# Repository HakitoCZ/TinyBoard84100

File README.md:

# TinyBoard84100

Tiny beakout board for the ATtiny841 (or any other 14 pin
AVR) with AVR ISP programming header, voltage regulated and
with reset button.

It is programmable with the Arduino IDE with the ATtiny
library addon thingy. Or a proper toolchain for all the
tryhard nerds out there :)

Designed in KiCAD open-source and possibly for sale on Tindie
somewhere in the future. No promisses.

It's actually a second version of the design, first was not
published nor tested. It was designed, manufactured and forgoten about.

If you're experienced and want to tell me how wrong I did
everything, feel free to PM me. I'm open to your feedback.

Q: What's so special about the ATtiny841?

A: Compared to ATtiny84, the ATtiny841 has one extra 16-bit
timer with two PWM channels, one more
ADC, more input channels, one extra comparator, one extra USART.
And for more details go check Microchip's product site.
If you want to build it yourself, ATtiny84 seem to be pin compatible
so you should be just fine using that if you want to shave off
few cents and/or don't need the extra functionality of 841.

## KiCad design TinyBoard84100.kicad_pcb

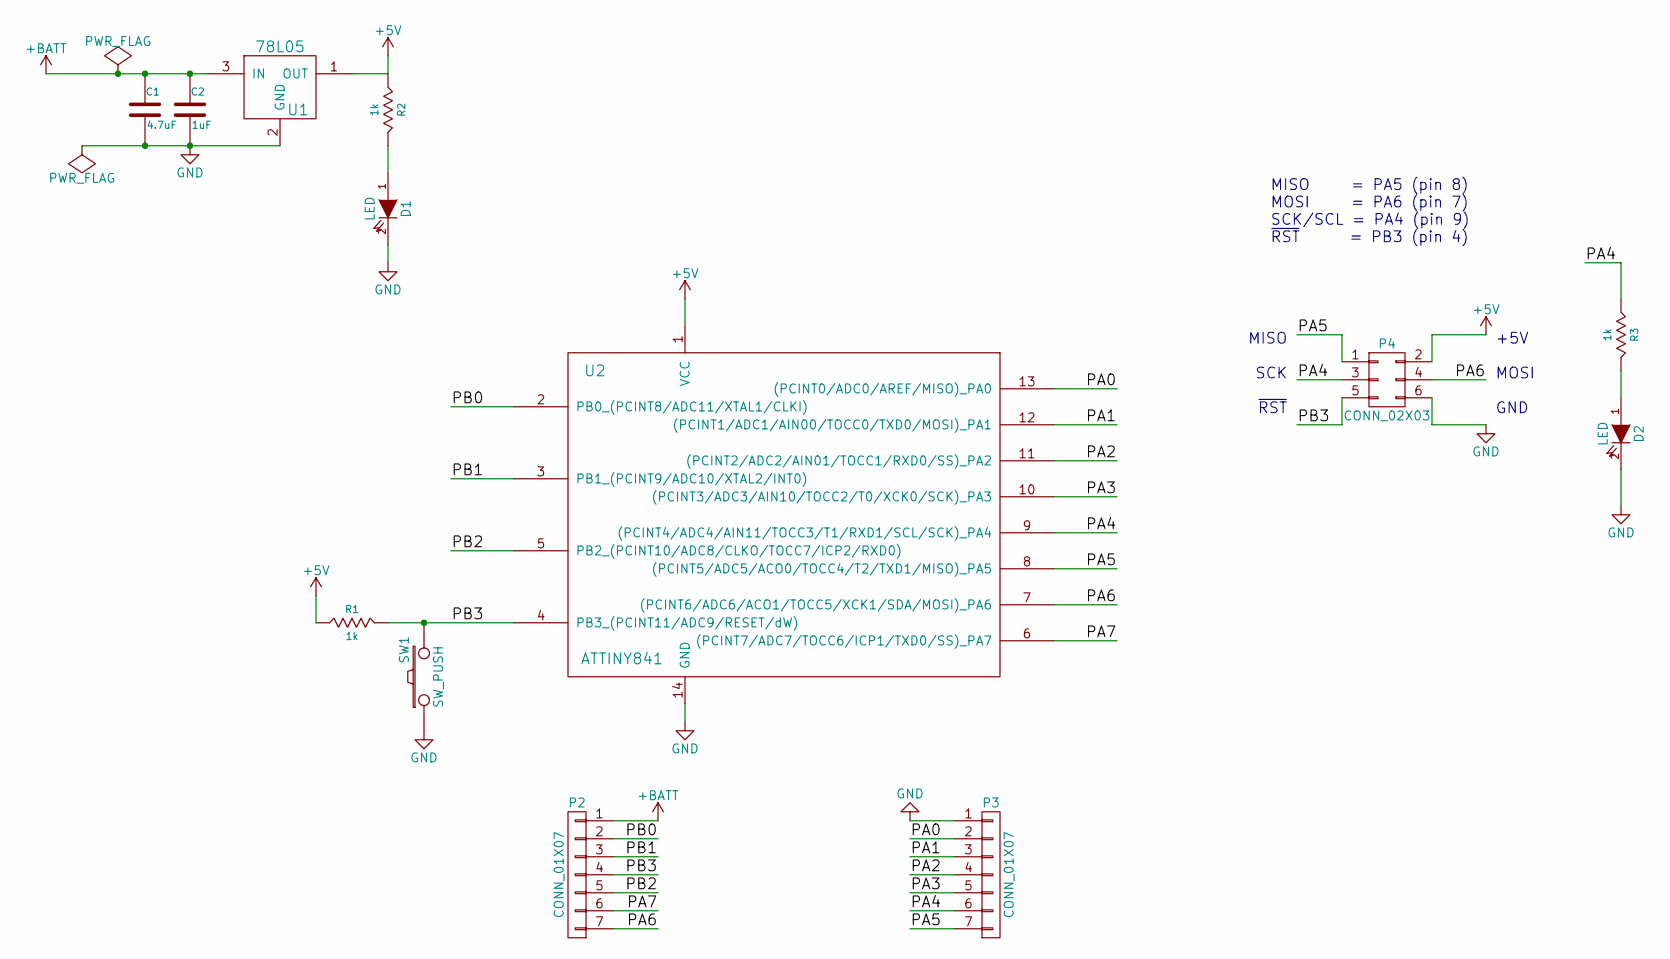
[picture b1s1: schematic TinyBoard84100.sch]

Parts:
C1: 4.7uF; C_1206_HandSoldering
C2: 1uF; C_1206_HandSoldering
D1, D2: LED; LED_0805
P2, P3: CONN_01X07; Pin_Header_Straight_1x07
P4: CONN_02X03; Pin_Header_Straight_2x03
R1, R2, R3: 1k; R_0805_HandSoldering
SW1: SW_PUSH; SW_SPST_FSMSM
U1: 78L05; SOT89-3_Housing_Handsoldering
U2: ATTINY841; SOIC-14_3.9x8.7mm_Pitch1.27mm

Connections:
+5V: P4.2, R1.1 (A), R2.1 (A), U1.1 (OUT), U2.1 (VCC)
+BATT: C1.1, C2.1, P2.1, U1.3 (IN)
/PA0: P3.2, U2.13 ((PCINT0/ADC0/AREF/MISO)_PA0)
/PA1: P3.3, U2.12 ((PCINT1/ADC1/AIN00/TOCC0/TXD0/MOSI)_PA1)
/PA2: P3.4, U2.11 ((PCINT2/ADC2/AIN01/TOCC1/RXD0/SS)_PA2)
/PA3: P3.5, U2.10 ((PCINT3/ADC3/AIN10/TOCC2/T0/XCK0/SCK)_P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)
/PA4: P3.6, P4.3, R3.1 (A), U2.9 ((PCINT4/ADC4/AIN11/TOCC3/T1/RXD1/SCL/SC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)
/PA5: P3.7, P4.1, U2.8 ((PCINT5/ADC5/ACO0/TOCC4/T2/TXD1/MISO)_P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)
/PA6: P2.7, P4.4, U2.7 ((PCINT6/ADC6/ACO1/TOCC5/XCK1/SDA/MOSI)_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)
/PA7: P2.6, U2.6 ((PCINT7/ADC7/TOCC6/ICP1/TXD0/SS)_PA7)
/PB0: P2.2, U2.2 (PB0_(PCINT8/ADC11/XTAL1/CLKI))
/PB1: P2.3, U2.3 (PB1_(PCINT9/ADC10/XTAL2/INT0))
/PB2: P2.5, U2.5 (PB2_(PCINT10/ADC8/CLKO/TOCC7/ICP2/RXD0))
/PB3: P2.4, P4.5, R1.2 (K), SW1.2, U2.4 (PB3_(PCINT11/ADC9/RESET/dW))
GND: C1.2, C2.2, D1.2 (K), D2.2 (K), P3.1, P4.6, SW1.1, U1.2 (GND), U2.14 (GND)
unnamed: D1.1 (A), R2.2 (K)
unnamed: D2.1 (A), R3.2 (K)

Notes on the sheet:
MISO SCK ~RST
+5V MOSI GND
MISO = PA5 (pin 8) MOSI = PA6 (pin 7) SCK/SCL = PA4 (pin 9) ~RST~ = PB3 (pin 4)

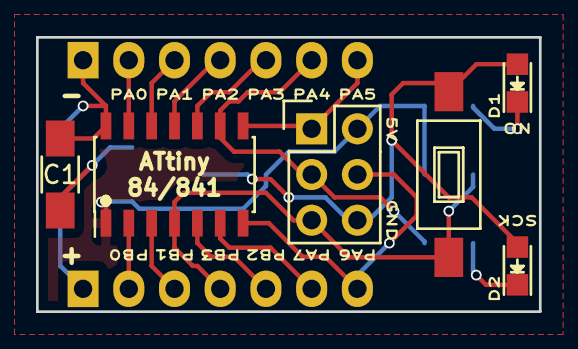
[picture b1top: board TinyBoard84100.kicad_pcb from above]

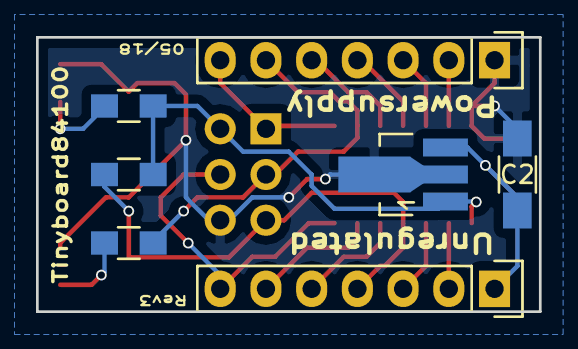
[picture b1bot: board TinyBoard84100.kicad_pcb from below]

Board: 2 copper layers, 27.9 x 15.2 mm, 13 parts (7 on the bottom side), 17 nets.

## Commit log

2018-04-14 init
2018-04-14 test
2018-04-15 Wiring ideas
2018-04-15 Wires and lables
2018-04-15 more wires and labels
2018-04-15 finishing schematic
2018-04-15 annotated & erc passed
2018-04-15 generated netlist & bom
2018-04-15 footprints associated
2018-04-15 new pcb with footprints
2018-04-15 First layout
2018-04-15 fixed zone connections
2018-04-15 gerbers
2018-04-17 silkscreen edits
2018-04-17 minimizing
2018-04-17 various exports
2018-04-17 touch
2018-04-17 regenerated
2018-04-29 corrected footprints
2018-04-29 update warning
2018-05-01 starting over
2018-05-01 first ideas
2018-05-01 condensation
2018-05-01 almost finished layout
2018-05-01 layout finished
2018-05-01 updated gerbers
2018-05-01 screenshot
2018-05-02 finishing touches
2018-05-02 generation
